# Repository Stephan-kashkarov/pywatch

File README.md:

# pywatch
A Smartwatch developed from scratch with an ESP8266EX microprocessor running micropython

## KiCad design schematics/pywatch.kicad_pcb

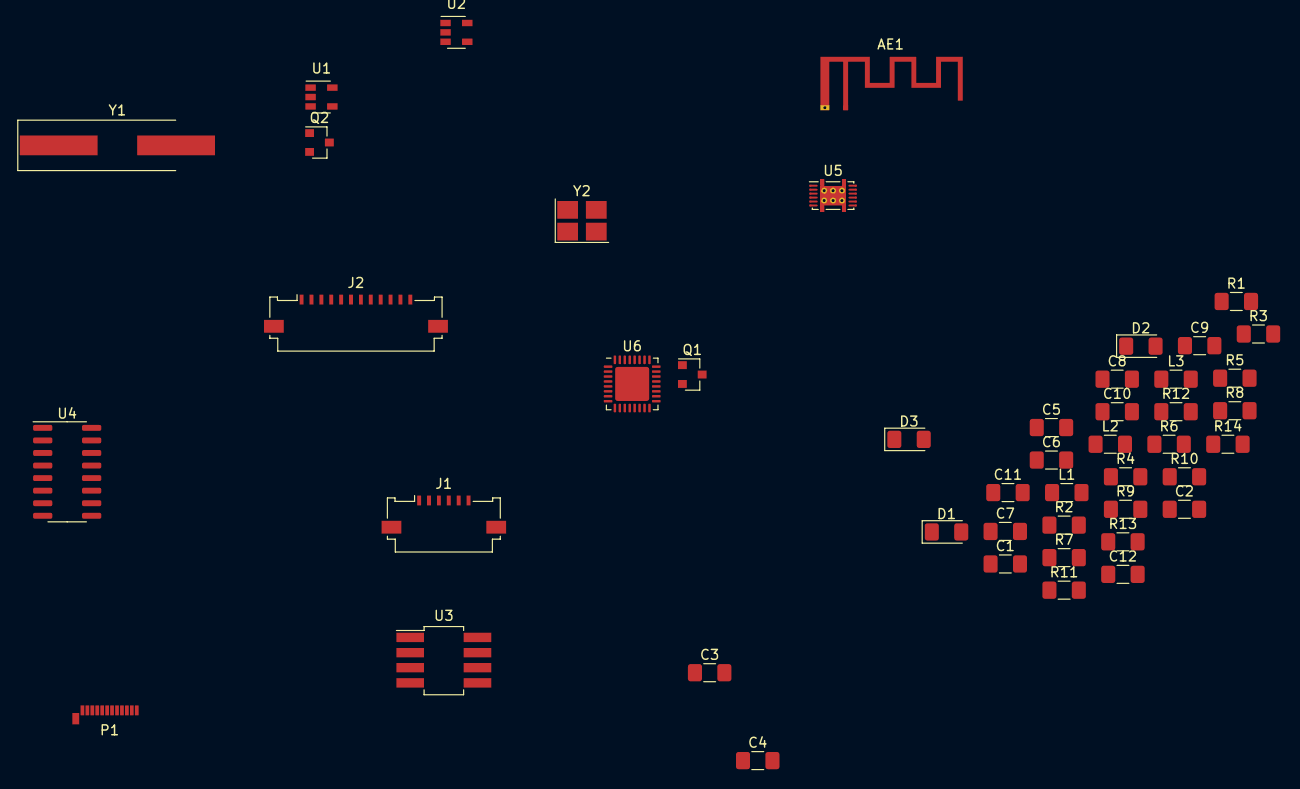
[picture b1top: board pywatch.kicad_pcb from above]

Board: 2 copper layers, 46 parts (0 on the bottom side), 39 nets, no tracks yet.

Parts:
AE1: Antenna_Loop; Texas_SWRA117D_2.4GHz_Right
C1, C2, C3, C4, C5, C6, C7, C8, C9, C10, C11, C12: C_Small; C_1206_3216Metric_Pad1.42x1.75mm_HandSolder
D1: D_Schottky_Small; D_1206_3216Metric_Pad1.42x1.75mm_HandSolder
D2, D3: LED_Small; LED_1206_3216Metric_Pad1.42x1.75mm_HandSolder
J1: Conn_01x06_Female; Molex_200528-0060_1x06-1MP_P1.00mm_Horizontal
J2: Conn_01x12_Female; Molex_200528-0120_1x12-1MP_P1.00mm_Horizontal
L1, L2, L3: L_Small; L_1206_3216Metric_Pad1.42x1.75mm_HandSolder
P1: USB_C_Plug_USB2.0; USB_C_Plug_Molex_105444
Q1, Q2: BC818; SOT-23
R1, R2, R3, R4, R6, R7, R8, R9, R10, R11, R12, R13, R14: R_Small_US; R_1206_3216Metric_Pad1.42x1.75mm_HandSolder
R5: R_Shunt_US; R_1206_3216Metric_Pad1.42x1.75mm_HandSolder
U1: MCP73812T-420I-OT; SOT-23-5
U2: LM27313XMF; SOT-23-5
U3: AT25DF041x-UxN-x; SOT-223-8
U4: CH340G; SOIC-16_3.9x9.9mm_P1.27mm
U5: BQ27441DRZR-G1A; Texas_S-PDSO-N12
U6: ESP8266EX; QFN-32-1EP_5x5mm_P0.5mm_EP3.45x3.45mm
Y1: Crystal_Small; Crystal_SMD_HC49-SD_HandSoldering
Y2: Crystal_GND24; Crystal_SMD_SeikoEpson_FA238-4Pin_3.2x2.5mm_HandSoldering

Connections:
+3V3: C8.1, C9.1, C10.1, J2.3, J2.4, L2.2, R11.2, U4.4, U6.1, U6.7, U6.11, U6.17, U6.29, U6.30
+5V: C4.1, C5.1, D1.1, P1.A4, P1.A9, P1.B4, P1.B5, P1.B9, R4.1, U1.1, U1.4, U4.16, U5.5
GND: AE1.2, C1.2, C2.1, C3.2, C5.2, C6.2, C7.1, C8.2, C9.2, C10.2, C11.2, C12.2, J1.1, J2.1, J2.5, J2.6, J2.7, J2.12, P1.A1, P1.A12, P1.B1, P1.B12, P1.S1, R1.2, R3.1, R8.1, R9.2, R10.2, R12.2, R13.2, U1.2, U2.2, U4.1, U5.3, U5.13, U6.33, Y2.2, Y2.4
unnamed: AE1.1, C11.1, L3.1
unnamed: C2.2, L1.2, R2.2, R5.1, U1.3, U2.5, U5.6
unnamed: C1.1, U4.7, Y1.1
unnamed: C3.1, U4.8, Y1.2
unnamed: C4.2, R3.2, R4.2, U2.3
unnamed: C6.1, U6.28, Y2.1
unnamed: C7.2, U6.27, Y2.3
unnamed: C12.1, L3.2, U6.2
unnamed: D1.2, L1.1, U2.1
unnamed: D2.1, R12.1
unnamed: D2.2, J1.4, R14.2, U4.2, U5.1, U6.24
unnamed: D3.1, R13.1
unnamed: D3.2, U4.3, U6.25
unnamed: J1.2, J2.9, U5.2, U6.21
unnamed: J1.3, R10.1, R11.1
unnamed: J1.5, U6.10
unnamed: J1.6, U6.9
unnamed: J2.2, R8.2
unnamed: J2.8, U6.13
unnamed: J2.10, U6.12
unnamed: J2.11, U6.16
unnamed: L2.1, U6.3, U6.4
unnamed: P1.A6, U4.5
unnamed: P1.A7, U4.6
unnamed: Q1.1, R6.1
unnamed: Q1.2, R7.2, U4.14
unnamed: Q1.3, U6.15
unnamed: Q2.1, R7.1
unnamed: Q2.2, R6.2, U4.13
unnamed: Q2.3, U6.8, U6.32
unnamed: R1.1, U1.5
unnamed: R2.1, U2.4
unnamed: R5.2, U5.8
unnamed: R9.1, U5.10
unnamed: R14.1, U6.26
unnamed: U5.12, U6.14

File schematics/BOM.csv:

Reference, Quantity, Value, Footprint, Datasheet
AE1 ,1,"Antenna_Loop","RF_Antenna:Texas_SWRA117D_2.4GHz_Right","~"
BT1 ,1,"Battery_Cell","","~"
C6 C7 C1 C3 C5 C2 C4 C8 C9 C10 C12 C11 ,12,"C_Small","Capacitor_SMD:C_1206_3216Metric_Pad1.42x1.75mm_HandSolder","~"
D1 ,1,"D_Schottky_Small","Diode_SMD:D_1206_3216Metric_Pad1.42x1.75mm_HandSolder","~"
D2 D3 ,2,"LED_Small","LED_SMD:LED_1206_3216Metric_Pad1.42x1.75mm_HandSolder","~"
J1 ,1,"Conn_01x06_Female","Connector_FFC-FPC:Molex_200528-0060_1x06-1MP_P1.00mm_Horizontal","~"
J2 ,1,"Conn_01x12_Female","Connector_FFC-FPC:Molex_200528-0120_1x12-1MP_P1.00mm_Horizontal","~"
L2 L1 L3 ,3,"L_Small","Inductor_SMD:L_1206_3216Metric_Pad1.42x1.75mm_HandSolder","~"
P1 ,1,"USB_C_Plug_USB2.0","Connector_USB:USB_C_Plug_Molex_105444","https://www.usb.org/sites/default/files/documents/usb_type-c.zip"
Q1 Q2 ,2,"BC818","Package_TO_SOT_SMD:SOT-23","https://www.fairchildsemi.com/datasheets/BC/BC818.pdf"
R12 R13 R14 R6 R7 R8 R11 R10 R9 R1 R2 R4 R3 ,13,"R_Small_US","Resistor_SMD:R_1206_3216Metric_Pad1.42x1.75mm_HandSolder","~"
R5 ,1,"R_Shunt_US","Resistor_SMD:R_1206_3216Metric_Pad1.42x1.75mm_HandSolder","~"
U1 ,1,"MCP73812T-420I-OT","Package_TO_SOT_SMD:SOT-23-5","http://ww1.microchip.com/downloads/en/DeviceDoc/22036b.pdf"
U2 ,1,"LM27313XMF","Package_TO_SOT_SMD:SOT-23-5","http://www.ti.com/lit/ds/symlink/lm27313.pdf"
U3 ,1,"AT25DF041x-UxN-x","Package_TO_SOT_SMD:SOT-223-8","http://www.adestotech.com/wp-content/uploads/DS-AT25DF041B_040.pdf"
U4 ,1,"CH340G","Package_SO:SOIC-16_3.9x9.9mm_P1.27mm","http://www.datasheet5.com/pdf-local-2195953"
U5 ,1,"BQ27441DRZR-G1A","Package_SON:Texas_S-PDSO-N12","http://www.ti.com/lit/ds/symlink/bq27441-g1.pdf"
U6 ,1,"ESP8266EX","Package_DFN_QFN:QFN-32-1EP_5x5mm_P0.5mm_EP3.45x3.45mm","http://espressif.com/sites/default/files/documentation/0a-es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"
Y1 ,1,"Crystal_Small","Crystal:Crystal_SMD_HC49-SD_HandSoldering","~"
Y2 ,1,"Crystal_GND24","Crystal:Crystal_SMD_SeikoEpson_FA238-4Pin_3.2x2.5mm_HandSoldering","~"

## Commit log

2019-07-14 added basic schematics
2019-07-14 added a few connections
2019-07-16 added majority of circuit
2019-07-16 completed schematic
2019-07-16 added boundry boxes to sch
2019-07-17 started pcb design
2019-07-22 added python binary to work folders
2019-07-25 started formula
2019-07-25 moved engine stuff into engine.py
2019-07-25 made static component base class
2019-07-30 fleshed out button class
2019-07-30 changed a keyword
2019-08-01 added device and modified how engine works
2019-08-01 lol idk
2019-08-01 added bitmap class
2019-08-01 added the thingo
2019-08-01 i just want a demo its getting late
2019-08-01 worked on ordering components
2019-08-01 not fully sure what happened
2019-09-10 Ahhhhhhh
